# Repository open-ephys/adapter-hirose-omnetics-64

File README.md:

# omnetics-adapter-64
Adapter board for using omnetics-based EIBs with headstage-64, headstage-64s, etc.

## Pinout
The adapter pinout is located on [this google
sheet](https://docs.google.com/spreadsheets/d/11wRDYOqHN5lPb03yUdfXfK0zvaDYsVetplaNK-R90Gg/edit#gid=1490495645)

## License
CC BY-SA-NC 4.0

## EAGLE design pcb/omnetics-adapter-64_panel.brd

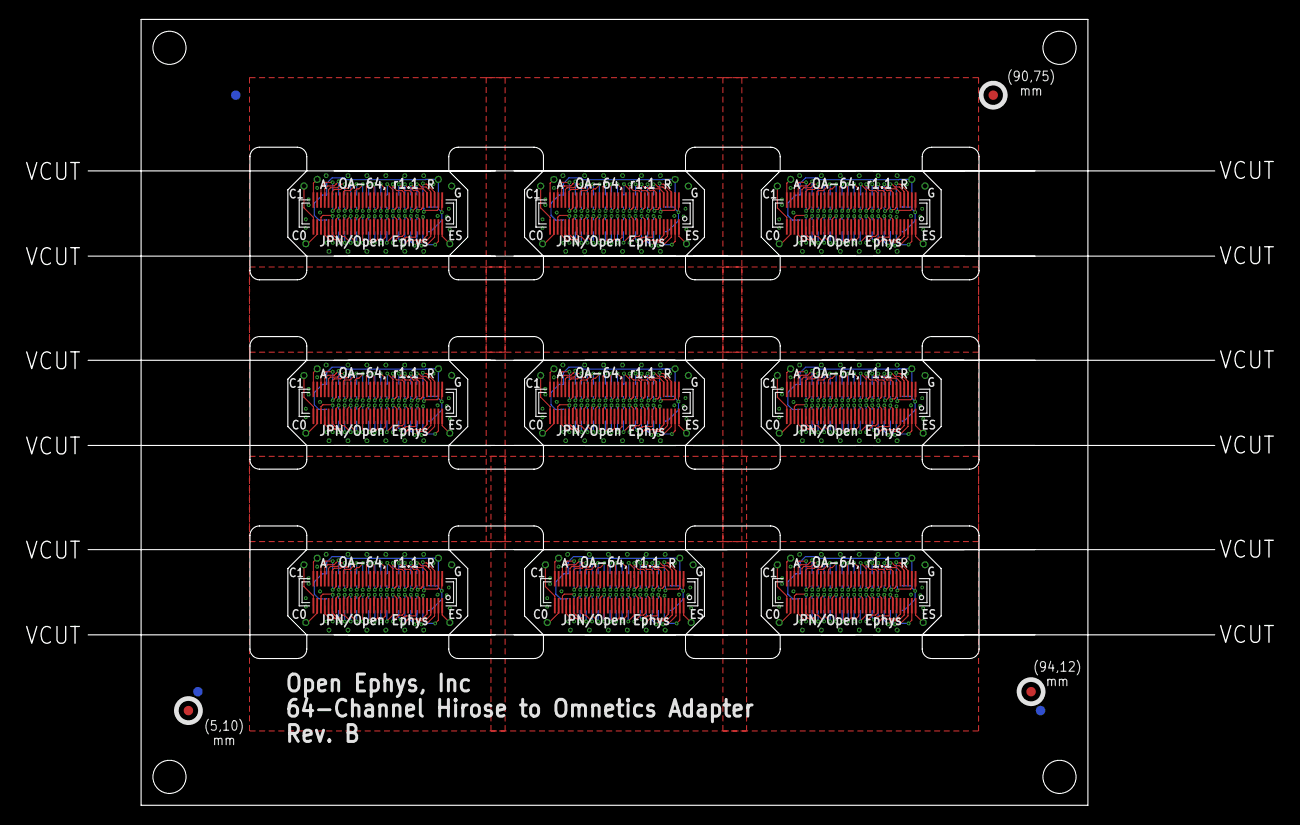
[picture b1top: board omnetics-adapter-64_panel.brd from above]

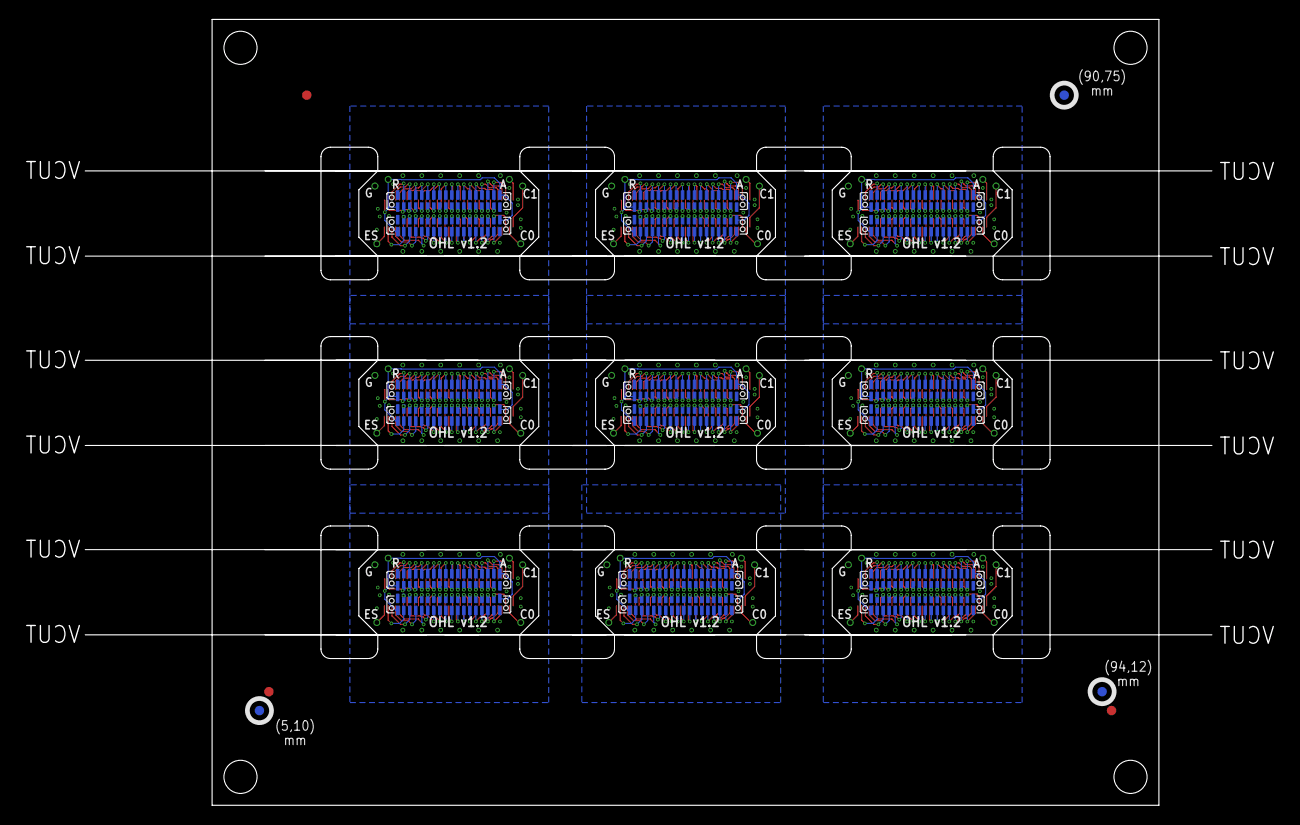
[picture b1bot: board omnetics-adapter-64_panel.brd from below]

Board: 2 copper layers, 100.0 x 83.0 mm, 87 parts (21 on the bottom side), 630 nets.

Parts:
AN, AN1, AN2, AN3, AN4, AN5, AN6, AN7, AN8: LRG_GP; GOLDPIN_0.5ID_0.7OD
CAT0, CAT1, CAT2, CAT3, CAT4, CAT5, CAT6, CAT7, CAT8, CAT9, CAT10, CAT11, CAT12, CAT13, CAT14, CAT15, CAT16, CAT17: LRG_GP; GOLDPIN_0.5ID_0.7OD
E$1, E$2, E$3, E$4, E$5, E$6: FIDUCIAL
ESTIM, ESTIM1, ESTIM2, ESTIM3, ESTIM4, ESTIM5, ESTIM6, ESTIM7, ESTIM8, ESTIM9, ESTIM10, ESTIM11, ESTIM12, ESTIM13, ESTIM14, ESTIM15, ESTIM16, ESTIM17, ESTIM18, ESTIM19, ESTIM20, ESTIM21, ESTIM22, ESTIM23, ESTIM24, ESTIM25, ESTIM26: LRG_GP; GOLDPIN_0.5ID_0.7OD
J1, J4, J7, J10, J13, J16, J19, J22, J25: DF40-REC; DDF40-70REC-LRG
J2, J3, J5, J6, J8, J9, J11, J12, J14, J15, J17, J18, J20, J21, J23, J24, J26, J27: NPD-36-VV-GS

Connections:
AN: AN.P$1, J1.36
AN1: AN1.P$1, J4.36
AN2: AN2.P$1, J7.36
AN3: AN3.P$1, J10.36
AN4: AN4.P$1, J13.36
AN5: AN5.P$1, J16.36
AN6: AN6.P$1, J19.36
AN7: AN7.P$1, J22.36
AN8: AN8.P$1, J25.36
CAT0: CAT0.P$1, J1.34
CAT1: CAT1.P$1, J1.35
CAT2: CAT2.P$1, J4.34
CAT3: CAT3.P$1, J4.35
CAT4: CAT4.P$1, J7.34
CAT5: CAT5.P$1, J7.35
CAT6: CAT6.P$1, J10.34
CAT7: CAT7.P$1, J10.35
CAT8: CAT8.P$1, J13.34
CAT9: CAT9.P$1, J13.35
CAT10: CAT10.P$1, J16.34
CAT11: CAT11.P$1, J16.35
CAT12: CAT12.P$1, J19.34
CAT13: CAT13.P$1, J19.35
CAT14: CAT14.P$1, J22.34
CAT15: CAT15.P$1, J22.35
CAT16: CAT16.P$1, J25.34
CAT17: CAT17.P$1, J25.35
ESTIM: ESTIM.P$1, J1.1
ESTIM1: ESTIM3.P$1, J4.1
ESTIM2: ESTIM6.P$1, J7.1
ESTIM3: ESTIM9.P$1, J10.1
ESTIM4: ESTIM12.P$1, J13.1
ESTIM5: ESTIM15.P$1, J16.1
ESTIM6: ESTIM18.P$1, J19.1
ESTIM7: ESTIM21.P$1, J22.1
ESTIM8: ESTIM24.P$1, J25.1
GND: ESTIM5.P$1, J4.37, J5.18, J5.36, J6.18, J6.36
GND1: ESTIM2.P$1, J1.37, J2.18, J2.36, J3.18, J3.36
GND2: ESTIM8.P$1, J7.37, J8.18, J8.36, J9.18, J9.36
GND3: ESTIM11.P$1, J10.37, J11.18, J11.36, J12.18, J12.36
GND4: ESTIM14.P$1, J13.37, J14.18, J14.36, J15.18, J15.36
GND5: ESTIM17.P$1, J16.37, J17.18, J17.36, J18.18, J18.36
GND6: ESTIM20.P$1, J19.37, J20.18, J20.36, J21.18, J21.36
GND7: ESTIM23.P$1, J22.37, J23.18, J23.36, J24.18, J24.36
GND8: ESTIM26.P$1, J25.37, J26.18, J26.36, J27.18, J27.36
unnamed: J1.69, J2.20
unnamed: J1.66, J2.15
unnamed: J1.67, J2.16
unnamed: J1.68, J2.17
unnamed: J1.65, J2.21
unnamed: J1.64, J2.14
unnamed: J1.63, J2.22
unnamed: J1.61, J2.23
unnamed: J1.62, J2.13
unnamed: J1.59, J2.24
unnamed: J1.58, J2.25
unnamed: J1.60, J2.12
unnamed: J1.56, J2.26
unnamed: J1.57, J2.11
unnamed: J1.54, J2.27
unnamed: J1.55, J2.10
unnamed: J1.53, J2.28
unnamed: J1.52, J2.9
unnamed: J1.51, J2.29
unnamed: J1.50, J2.8
unnamed: J1.49, J2.30
unnamed: J1.48, J2.31
unnamed: J1.47, J2.7
unnamed: J1.46, J2.32
unnamed: J1.45, J2.33
unnamed: J1.44, J2.6
unnamed: J1.43, J2.34
unnamed: J1.42, J2.35
unnamed: J1.41, J2.5
unnamed: J1.40, J2.4
unnamed: J1.39, J2.3
unnamed: J1.38, J2.2
unnamed: J1.5, J3.23
unnamed: J1.4, J3.22
unnamed: J1.3, J3.21
unnamed: J1.2, J3.20
unnamed: J1.33, J3.2
unnamed: J4.32, J6.35
unnamed: J4.31, J6.34
unnamed: J4.30, J6.33
unnamed: J4.29, J6.3
unnamed: J4.28, J6.32
unnamed: J4.27, J6.4
unnamed: J4.26, J6.5
unnamed: J4.25, J6.31
unnamed: J4.24, J6.6
unnamed: J4.23, J6.7
unnamed: J4.22, J6.30
unnamed: J4.21, J6.8
unnamed: J4.20, J6.29
unnamed: J4.19, J6.9
unnamed: J4.18, J6.28
unnamed: J4.17, J6.10
unnamed: J4.16, J6.27
unnamed: J4.15, J6.11
unnamed: J4.14, J6.26
unnamed: J4.13, J6.12
unnamed: J4.12, J6.13
unnamed: J4.11, J6.25
unnamed: J4.10, J6.14
unnamed: J4.9, J6.15
unnamed: J4.8, J6.24
unnamed: J4.7, J6.16
unnamed: J4.6, J6.17
unnamed: J4.69, J5.20
unnamed: J4.67, J5.16
unnamed: J4.65, J5.21
unnamed: J4.64, J5.14
unnamed: J4.63, J5.22
unnamed: J4.61, J5.23
unnamed: J4.62, J5.13
unnamed: J4.59, J5.24
unnamed: J4.58, J5.25
unnamed: J4.60, J5.12
unnamed: J4.56, J5.26
unnamed: J4.57, J5.11
unnamed: J4.54, J5.27
unnamed: J4.55, J5.10
unnamed: J4.53, J5.28
unnamed: J4.52, J5.9
unnamed: J4.51, J5.29
unnamed: J4.50, J5.8
unnamed: J4.49, J5.30
unnamed: J4.48, J5.31
unnamed: J4.47, J5.7
unnamed: J4.46, J5.32
unnamed: J4.45, J5.33
unnamed: J4.44, J5.6
unnamed: J4.43, J5.34
unnamed: J4.42, J5.35
unnamed: J4.41, J5.5
unnamed: J4.39, J5.3
unnamed: J4.5, J6.23
unnamed: J4.4, J6.22
unnamed: J4.3, J6.21
unnamed: J4.2, J6.20
unnamed: J4.66, J5.15
unnamed: J4.68, J5.17
unnamed: J4.40, J5.4
unnamed: J4.38, J5.2
unnamed: J4.33, J6.2
unnamed: J7.32, J9.35
unnamed: J7.31, J9.34
unnamed: J7.30, J9.33
unnamed: J7.29, J9.3
unnamed: J7.28, J9.32
unnamed: J7.27, J9.4
unnamed: J7.26, J9.5
unnamed: J7.25, J9.31
unnamed: J7.24, J9.6
unnamed: J7.23, J9.7
unnamed: J7.22, J9.30
unnamed: J7.21, J9.8
unnamed: J7.20, J9.29
unnamed: J7.19, J9.9
unnamed: J7.18, J9.28
unnamed: J7.17, J9.10
unnamed: J7.16, J9.27
unnamed: J7.15, J9.11
unnamed: J7.14, J9.26
unnamed: J7.13, J9.12
unnamed: J7.12, J9.13
unnamed: J7.11, J9.25
unnamed: J7.10, J9.14
unnamed: J7.9, J9.15
unnamed: J7.8, J9.24
unnamed: J7.7, J9.16
unnamed: J7.6, J9.17
unnamed: J7.69, J8.20
unnamed: J7.67, J8.16
unnamed: J7.65, J8.21
unnamed: J7.64, J8.14
unnamed: J7.63, J8.22
unnamed: J7.61, J8.23
unnamed: J7.62, J8.13
unnamed: J7.59, J8.24
unnamed: J7.58, J8.25
unnamed: J7.60, J8.12
unnamed: J7.56, J8.26
unnamed: J7.57, J8.11
unnamed: J7.54, J8.27
unnamed: J7.55, J8.10
unnamed: J7.53, J8.28
unnamed: J7.52, J8.9
unnamed: J7.51, J8.29
unnamed: J7.50, J8.8
unnamed: J7.49, J8.30
unnamed: J7.48, J8.31
unnamed: J7.47, J8.7
unnamed: J7.46, J8.32
unnamed: J7.45, J8.33
unnamed: J7.44, J8.6
unnamed: J7.43, J8.34
unnamed: J7.42, J8.35
unnamed: J7.41, J8.5
unnamed: J7.39, J8.3
unnamed: J7.5, J9.23
unnamed: J7.4, J9.22
unnamed: J7.3, J9.21
unnamed: J7.2, J9.20
unnamed: J7.66, J8.15
unnamed: J7.68, J8.17
unnamed: J7.40, J8.4
unnamed: J7.38, J8.2
unnamed: J7.33, J9.2
unnamed: J10.32, J12.35
unnamed: J10.31, J12.34
unnamed: J10.30, J12.33
unnamed: J10.29, J12.3
unnamed: J10.28, J12.32
unnamed: J10.27, J12.4
unnamed: J10.26, J12.5
unnamed: J10.25, J12.31
unnamed: J10.24, J12.6
unnamed: J10.23, J12.7
unnamed: J10.22, J12.30
unnamed: J10.21, J12.8
unnamed: J10.20, J12.29
unnamed: J10.19, J12.9
unnamed: J10.18, J12.28
unnamed: J10.17, J12.10
unnamed: J10.16, J12.27
unnamed: J10.15, J12.11
unnamed: J10.14, J12.26
unnamed: J10.13, J12.12
unnamed: J10.12, J12.13
unnamed: J10.11, J12.25
unnamed: J10.10, J12.14
unnamed: J10.9, J12.15
unnamed: J10.8, J12.24
unnamed: J10.7, J12.16
unnamed: J10.6, J12.17
unnamed: J10.69, J11.20
unnamed: J10.67, J11.16
unnamed: J10.65, J11.21
unnamed: J10.64, J11.14
unnamed: J10.63, J11.22
unnamed: J10.61, J11.23
unnamed: J10.62, J11.13
unnamed: J1.32, J3.35
unnamed: J1.31, J3.34
unnamed: J1.30, J3.33
unnamed: J1.29, J3.3
unnamed: J1.28, J3.32
unnamed: J1.27, J3.4
unnamed: J1.26, J3.5
unnamed: J1.25, J3.31
unnamed: J1.24, J3.6
unnamed: J1.23, J3.7
unnamed: J1.22, J3.30
unnamed: J1.21, J3.8
unnamed: J1.20, J3.29
unnamed: J1.19, J3.9
unnamed: J1.18, J3.28
unnamed: J1.17, J3.10
unnamed: J1.16, J3.27
unnamed: J1.15, J3.11
unnamed: J1.14, J3.26
unnamed: J1.13, J3.12
unnamed: J1.12, J3.13
unnamed: J1.11, J3.25
unnamed: J1.10, J3.14
unnamed: J1.9, J3.15
unnamed: J1.8, J3.24
unnamed: J1.7, J3.16
unnamed: J1.6, J3.17
unnamed: J10.59, J11.24
unnamed: J10.58, J11.25
unnamed: J10.60, J11.12
unnamed: J10.56, J11.26
unnamed: J10.57, J11.11
unnamed: J10.54, J11.27
unnamed: J10.55, J11.10
unnamed: J10.53, J11.28
unnamed: J10.52, J11.9
unnamed: J10.51, J11.29
unnamed: J10.50, J11.8
unnamed: J10.49, J11.30
unnamed: J10.48, J11.31
unnamed: J10.47, J11.7
unnamed: J10.46, J11.32
unnamed: J10.45, J11.33
unnamed: J10.44, J11.6
unnamed: J10.43, J11.34
unnamed: J10.42, J11.35
unnamed: J10.41, J11.5
unnamed: J10.39, J11.3
unnamed: J10.5, J12.23
unnamed: J10.4, J12.22
unnamed: J10.3, J12.21
unnamed: J10.2, J12.20
unnamed: J10.66, J11.15
unnamed: J10.68, J11.17
unnamed: J10.40, J11.4
unnamed: J10.38, J11.2
unnamed: J10.33, J12.2
unnamed: J13.32, J15.35
unnamed: J13.31, J15.34
unnamed: J13.30, J15.33
unnamed: J13.29, J15.3
unnamed: J13.28, J15.32
unnamed: J13.27, J15.4
unnamed: J13.26, J15.5
unnamed: J13.25, J15.31
unnamed: J13.24, J15.6
unnamed: J13.23, J15.7
unnamed: J13.22, J15.30
unnamed: J13.21, J15.8
unnamed: J13.20, J15.29
unnamed: J13.19, J15.9
unnamed: J13.18, J15.28
unnamed: J13.17, J15.10
unnamed: J13.16, J15.27
unnamed: J13.15, J15.11
unnamed: J13.14, J15.26
unnamed: J13.13, J15.12
unnamed: J13.12, J15.13
unnamed: J13.11, J15.25
unnamed: J13.10, J15.14
unnamed: J13.9, J15.15
unnamed: J13.8, J15.24
unnamed: J13.7, J15.16
unnamed: J13.6, J15.17
unnamed: J13.69, J14.20
unnamed: J13.67, J14.16
unnamed: J13.65, J14.21
unnamed: J13.64, J14.14
unnamed: J13.63, J14.22
unnamed: J13.61, J14.23
unnamed: J13.62, J14.13
unnamed: J13.59, J14.24
unnamed: J13.58, J14.25
unnamed: J13.60, J14.12
unnamed: J13.56, J14.26
unnamed: J13.57, J14.11
unnamed: J13.54, J14.27
unnamed: J13.55, J14.10
unnamed: J13.53, J14.28
unnamed: J13.52, J14.9
unnamed: J13.51, J14.29
unnamed: J13.50, J14.8
unnamed: J13.49, J14.30
unnamed: J13.48, J14.31
unnamed: J13.47, J14.7
unnamed: J13.46, J14.32
unnamed: J13.45, J14.33
unnamed: J13.44, J14.6
unnamed: J13.43, J14.34
unnamed: J13.42, J14.35
unnamed: J13.41, J14.5
unnamed: J13.39, J14.3
unnamed: J13.5, J15.23
unnamed: J13.4, J15.22
unnamed: J13.3, J15.21
unnamed: J13.2, J15.20
unnamed: J13.66, J14.15
unnamed: J13.68, J14.17
unnamed: J13.40, J14.4
unnamed: J13.38, J14.2
unnamed: J13.33, J15.2
unnamed: J16.32, J18.35
unnamed: J16.31, J18.34
unnamed: J16.30, J18.33
unnamed: J16.29, J18.3
unnamed: J16.28, J18.32
unnamed: J16.27, J18.4
unnamed: J16.26, J18.5
unnamed: J16.25, J18.31
unnamed: J16.24, J18.6
unnamed: J16.23, J18.7
unnamed: J16.22, J18.30
unnamed: J16.21, J18.8
unnamed: J16.20, J18.29
unnamed: J16.19, J18.9
unnamed: J16.18, J18.28
unnamed: J16.17, J18.10
unnamed: J16.16, J18.27
unnamed: J16.15, J18.11
unnamed: J16.14, J18.26
unnamed: J16.13, J18.12
unnamed: J16.12, J18.13
unnamed: J16.11, J18.25
unnamed: J16.10, J18.14
unnamed: J16.9, J18.15
unnamed: J16.8, J18.24
unnamed: J16.7, J18.16
unnamed: J16.6, J18.17
unnamed: J16.69, J17.20
unnamed: J16.67, J17.16
unnamed: J16.65, J17.21
unnamed: J16.64, J17.14
unnamed: J16.63, J17.22
unnamed: J16.61, J17.23
unnamed: J16.62, J17.13
unnamed: J16.59, J17.24
unnamed: J16.58, J17.25
unnamed: J16.60, J17.12
unnamed: J16.56, J17.26
unnamed: J16.57, J17.11
unnamed: J16.54, J17.27
unnamed: J16.55, J17.10
unnamed: J16.53, J17.28
unnamed: J16.52, J17.9
unnamed: J16.51, J17.29
unnamed: J16.50, J17.8
unnamed: J16.49, J17.30
unnamed: J16.48, J17.31
unnamed: J16.47, J17.7
unnamed: J16.46, J17.32
unnamed: J16.45, J17.33
unnamed: J16.44, J17.6
unnamed: J16.43, J17.34
unnamed: J16.42, J17.35
unnamed: J16.41, J17.5
unnamed: J16.39, J17.3
unnamed: J16.5, J18.23
unnamed: J16.4, J18.22
unnamed: J16.3, J18.21
unnamed: J16.2, J18.20
unnamed: J16.66, J17.15
unnamed: J16.68, J17.17
unnamed: J16.40, J17.4
unnamed: J16.38, J17.2
unnamed: J16.33, J18.2
unnamed: J19.32, J21.35
unnamed: J19.31, J21.34
unnamed: J19.30, J21.33
unnamed: J19.29, J21.3
unnamed: J19.28, J21.32
unnamed: J19.27, J21.4
unnamed: J19.26, J21.5
unnamed: J19.25, J21.31
unnamed: J19.24, J21.6
unnamed: J19.23, J21.7
unnamed: J19.22, J21.30
unnamed: J19.21, J21.8
unnamed: J19.20, J21.29
unnamed: J19.19, J21.9
unnamed: J19.18, J21.28
unnamed: J19.17, J21.10
unnamed: J19.16, J21.27
unnamed: J19.15, J21.11
unnamed: J19.14, J21.26
unnamed: J19.13, J21.12
unnamed: J19.12, J21.13
unnamed: J19.11, J21.25
unnamed: J19.10, J21.14
unnamed: J19.9, J21.15
unnamed: J19.8, J21.24
unnamed: J19.7, J21.16
unnamed: J19.6, J21.17
unnamed: J19.69, J20.20
unnamed: J19.67, J20.16
unnamed: J19.65, J20.21
unnamed: J19.64, J20.14
unnamed: J19.63, J20.22
unnamed: J19.61, J20.23
unnamed: J19.62, J20.13
unnamed: J19.59, J20.24
unnamed: J19.58, J20.25
unnamed: J19.60, J20.12
unnamed: J19.56, J20.26
unnamed: J19.57, J20.11
unnamed: J19.54, J20.27
unnamed: J19.55, J20.10
unnamed: J19.53, J20.28
unnamed: J19.52, J20.9
unnamed: J19.51, J20.29
unnamed: J19.50, J20.8
unnamed: J19.49, J20.30
unnamed: J19.48, J20.31
unnamed: J19.47, J20.7
unnamed: J19.46, J20.32
unnamed: J19.45, J20.33
unnamed: J19.44, J20.6
unnamed: J19.43, J20.34
unnamed: J19.42, J20.35
unnamed: J19.41, J20.5
unnamed: J19.39, J20.3
unnamed: J19.5, J21.23
unnamed: J19.4, J21.22
unnamed: J19.3, J21.21
unnamed: J19.2, J21.20
unnamed: J19.66, J20.15
unnamed: J19.68, J20.17
unnamed: J19.40, J20.4
unnamed: J19.38, J20.2
unnamed: J19.33, J21.2
unnamed: J22.32, J24.35
unnamed: J22.31, J24.34
unnamed: J22.30, J24.33
unnamed: J22.29, J24.3
unnamed: J22.28, J24.32
unnamed: J22.27, J24.4
unnamed: J22.26, J24.5
unnamed: J22.25, J24.31
unnamed: J22.24, J24.6
unnamed: J22.23, J24.7
unnamed: J22.22, J24.30
unnamed: J22.21, J24.8
unnamed: J22.20, J24.29
unnamed: J22.19, J24.9
unnamed: J22.18, J24.28
unnamed: J22.17, J24.10
unnamed: J22.16, J24.27
unnamed: J22.15, J24.11
unnamed: J22.14, J24.26
unnamed: J22.13, J24.12
unnamed: J22.12, J24.13
unnamed: J22.11, J24.25
unnamed: J22.10, J24.14
unnamed: J22.9, J24.15
unnamed: J22.8, J24.24
unnamed: J22.7, J24.16
unnamed: J22.6, J24.17
unnamed: J22.69, J23.20
unnamed: J22.67, J23.16
unnamed: J22.65, J23.21
unnamed: J22.64, J23.14
unnamed: J22.63, J23.22
unnamed: J22.61, J23.23
unnamed: J22.62, J23.13
unnamed: J22.59, J23.24
unnamed: J22.58, J23.25
unnamed: J22.60, J23.12
unnamed: J22.56, J23.26
unnamed: J22.57, J23.11
unnamed: J22.54, J23.27
unnamed: J22.55, J23.10
unnamed: J22.53, J23.28
unnamed: J22.52, J23.9
unnamed: J22.51, J23.29
unnamed: J22.50, J23.8
unnamed: J22.49, J23.30
unnamed: J22.48, J23.31
unnamed: J22.47, J23.7
unnamed: J22.46, J23.32
unnamed: J22.45, J23.33
unnamed: J22.44, J23.6
unnamed: J22.43, J23.34
unnamed: J22.42, J23.35
unnamed: J22.41, J23.5
unnamed: J22.39, J23.3
unnamed: J22.5, J24.23
unnamed: J22.4, J24.22
unnamed: J22.3, J24.21
unnamed: J22.2, J24.20
unnamed: J22.66, J23.15
unnamed: J22.68, J23.17
unnamed: J22.40, J23.4
unnamed: J22.38, J23.2
unnamed: J22.33, J24.2
unnamed: J25.32, J27.35
unnamed: J25.31, J27.34
unnamed: J25.30, J27.33
unnamed: J25.29, J27.3
unnamed: J25.28, J27.32
unnamed: J25.27, J27.4
unnamed: J25.26, J27.5
unnamed: J25.25, J27.31
unnamed: J25.24, J27.6
unnamed: J25.23, J27.7
unnamed: J25.22, J27.30
unnamed: J25.21, J27.8
unnamed: J25.20, J27.29
unnamed: J25.19, J27.9
unnamed: J25.18, J27.28
unnamed: J25.17, J27.10
unnamed: J25.16, J27.27
unnamed: J25.15, J27.11
unnamed: J25.14, J27.26
unnamed: J25.13, J27.12
unnamed: J25.12, J27.13
unnamed: J25.11, J27.25
unnamed: J25.10, J27.14
unnamed: J25.9, J27.15
unnamed: J25.8, J27.24
unnamed: J25.7, J27.16
unnamed: J25.6, J27.17
unnamed: J25.69, J26.20
unnamed: J25.67, J26.16
unnamed: J25.65, J26.21
unnamed: J25.64, J26.14
unnamed: J25.63, J26.22
unnamed: J25.61, J26.23
unnamed: J25.62, J26.13
unnamed: J25.59, J26.24
unnamed: J25.58, J26.25
unnamed: J25.60, J26.12
unnamed: J25.56, J26.26
unnamed: J25.57, J26.11
unnamed: J25.54, J26.27
unnamed: J25.55, J26.10
unnamed: J25.53, J26.28
unnamed: J25.52, J26.9
unnamed: J25.51, J26.29
unnamed: J25.50, J26.8
unnamed: J25.49, J26.30
unnamed: J25.48, J26.31
unnamed: J25.47, J26.7
unnamed: J25.46, J26.32
unnamed: J25.45, J26.33
unnamed: J25.44, J26.6
unnamed: J25.43, J26.34
unnamed: J25.42, J26.35
unnamed: J25.41, J26.5
unnamed: J25.39, J26.3
unnamed: J25.5, J27.23
unnamed: J25.4, J27.22
unnamed: J25.3, J27.21
unnamed: J25.2, J27.20
unnamed: J25.66, J26.15
unnamed: J25.68, J26.17
unnamed: J25.40, J26.4
unnamed: J25.38, J26.2
unnamed: J25.33, J27.2
REF: ESTIM1.P$1, J1.70, J2.1, J2.19, J3.1, J3.19
REF1: ESTIM4.P$1, J4.70, J5.1, J5.19, J6.1, J6.19
REF2: ESTIM7.P$1, J7.70, J8.1, J8.19, J9.1, J9.19
REF3: ESTIM10.P$1, J10.70, J11.1, J11.19, J12.1, J12.19
REF4: ESTIM13.P$1, J13.70, J14.1, J14.19, J15.1, J15.19
REF5: ESTIM16.P$1, J16.70, J17.1, J17.19, J18.1, J18.19
REF6: ESTIM19.P$1, J19.70, J20.1, J20.19, J21.1, J21.19
REF7: ESTIM22.P$1, J22.70, J23.1, J23.19, J24.1, J24.19
REF8: ESTIM25.P$1, J25.70, J26.1, J26.19, J27.1, J27.19

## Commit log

2023-02-08 Initial commit
    - Moved from ONI mega repo
2023-09-22 Replace design with 1.3 pinout
    - This pinout fits headstage-64 that is in the field
